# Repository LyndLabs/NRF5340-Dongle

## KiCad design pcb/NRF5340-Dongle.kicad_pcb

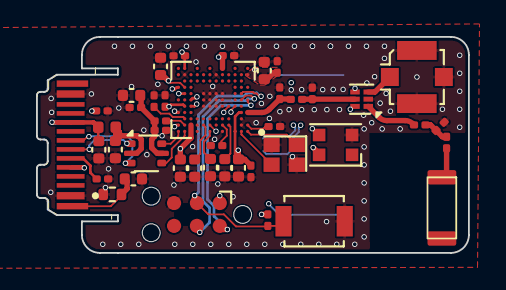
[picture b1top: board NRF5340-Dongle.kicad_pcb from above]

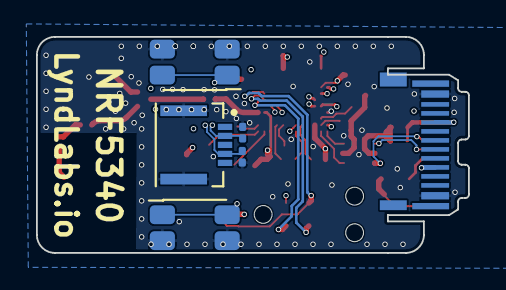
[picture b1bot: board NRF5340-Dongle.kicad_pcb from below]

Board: 4 copper layers, 24.0 x 12.0 mm, 48 parts (5 on the bottom side), 35 nets.

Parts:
AE1: 2450AT18B100
C1, C2, C3, C4, C6, C32, C46: 100nF; C_0201_0603Metric
C8, C9, C20, C30, C43, C45, C47, C47#2: 1uF; C_0402_1005Metric
C10, C16: 4.7uf; C_0201_0603Metric
C11, C21: .7pF; C_0201_0603Metric
C13: 2.2pF; C_0201_0603Metric
C18: NC; R_0201_0603Metric
C24: 4.7nF; C_0402_1005Metric
C25: 10nF; C_0402_1005Metric
C27: 100nF; C_0402_1005Metric
C41, C42: 300pF; C_0201_0603Metric
C44: 2.2nF; C_0201_0603Metric
D2: WS2812B-2020; LED_WS2812B-2020_PLCC4_2.0x2.0mm
J1: Molex 51281-0594; MOLEX_51281-0594
J3: SWD; Tag-Connect_TC2030-IDC-NL_2x03_P1.27mm_Vertical
J6: u.fl; U.FL_Molex_MCRF_73412-0110_Vertical
L1: 4.7nh; L_0201_0603Metric
L4: 2.2nH; L_0201_0603Metric
L5: 120R; L_0402_1005Metric
P1: USB_C_Plug; JAE_DX07P024AJ1R1500
R1: 2.2; R_0201_0603Metric
R2: 1M0; R_0402_1005Metric
R3: 10K; R_0201_0603Metric
R4, R5: 5.1K; R_0201_0603Metric
SW1, SW2: SW_Push; SW_SPST_EVQP7A
SW3: Reset; SW_SPST_B3U-1000P
U1: nRF5340-CLXX; NRF5340-4x4
U2: USBLC6-2P6; SOT-666
U3: DFN-6_1.3x1.2mm_P0.4mm
Y1: 32MHz; Crystal_SMD_2016-4Pin_2.0x1.6mm

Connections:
CC1: P1.A5 (CC), R5.1
DECR: C20.2, U1.B4 (DECR)
DIN+: P1.A6 (D+), U2.1 (I/O1)
DIN-: P1.A7 (D-), U2.3 (I/O2)
GND: C1.1, C2.1, C3.1, C4.1, C6.1, C8.1, C9.1, C10.2, C11.2, C16.2, C18.2, C20.1, C21.2, C24.2, C25.2, C27.2, C30.2, C32.2, C41.1, C42.2, C43.2, C44.2, C45.2, C46.2, C47.1, C47#2.1, D2.2 (VSS), J1.SH (Shield), J3.5 (GND), J6.2 (Ext), P1.A1 (GND), P1.A12 (GND), P1.B1 (GND), P1.B12 (GND), R2.2, R4.2, R5.2, SW1.2, SW2.2, SW3.2, U1.A5 (VSS), U1.B2 (VSS), U1.B9 (VSS), U1.C2 (VSS), U1.D12 (VSS), U1.E5 (VSS), U1.E6 (VSS), U1.E7 (VSS), U1.E8 (VSS), U1.F5 (VSS), U1.F6 (VSS), U1.F7 (VSS), U1.F8 (VSS), U1.G5 (AVSS), U1.G6 (VSS), U1.G7 (VSS), U1.G8 (VSS), U1.K6 (AVSS), U1.K11 (AVSS), U3.2 (GND), Y1.2, Y1.4
LED: D2.3 (DIN), U1.E3 (P0.28/AIN7)
NFC1: C41.2, J1.4, U1.G11 (P0.02/NFC1)
NFC2: C42.1, J1.2, U1.H12 (P0.03/NFC2)
unnamed: AE1.1 (A), L1.1
unnamed: C11.1, C13.1, L1.2
unnamed: C25.1, L5.1, P1.A4 (VBUS), P1.A9 (VBUS), P1.B4 (VBUS), P1.B9 (VBUS)
unnamed: J6.1 (In), U3.3 (RF1)
unnamed: C24.1, P1.S2, R2.1
unnamed: C21.1, L4.2, U1.D1 (ANT)
unnamed: U1.A1 (XC1), Y1.1
unnamed: U1.A2 (XC2), Y1.3
unnamed: C45.1, U1.B8 (DECA)
unnamed: C43.1, U1.A7 (DECD)
unnamed: C46.1, U1.B5 (DECN)
unnamed: C44.1, U1.B1 (DECRF)
unnamed: C16.1, U1.C11 (DECUSB)
unnamed: R1.1, U1.B11 (VBUS)
unnamed: C27.1, L5.2, U2.2 (GND)
unnamed: C18.1, L4.1, U3.5 (ANT)
unnamed: C13.2, U3.1 (RF2)
RST: J3.3 (~RESET), R3.1, SW3.1, U1.G2 (~RESET)
SWCLK: J3.4 (SWCLK), U1.F2 (SWDCLK)
SWDIO: J3.2 (SWDIO), U1.F1 (SWDIO)
USB_D+: U1.A12 (D+), U2.6 (I/O1)
USB_D-: U1.A11 (D-), U2.4 (I/O2)
VBUS: C10.1, C30.1, C32.1, R1.2, U2.5 (VBUS)
VCTL: U1.E4 (P1.10), U3.6 (VCTL)
VDD_NRF: C1.2, C2.2, C3.2, C4.2, C6.2, C8.2, C9.2, C47.2, C47#2.2, D2.4 (VDD), J3.1 (VCC), R3.2, U1.A3 (VDD), U1.B7 (VDD), U1.B10 (VDD), U1.B12 (VDDH), U1.D2 (VDD), U1.E11 (VDD), U1.H11 (VDD), U1.K1 (VDD), U1.L5 (VDD), U1.L11 (VDD), U3.4 (VDD)
VOL-A: SW1.1, U1.E10 (P1.01)
VOL-B: SW2.1, U1.F10 (P0.05/AIN1)

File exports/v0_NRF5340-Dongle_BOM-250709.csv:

Designator,Comment,Footprint,JLCPCB Part #
AE1,2450AT18B100,2450AT18B100,C2917717
"C1,C2,C4,C6,C7,C32,C46",100nF,201,C76934
"C8,C9,C20,C30,C43,C45,C47",1uF,402,C29266
"C10,C16",4.7uf,Capacitor_SMD:C_0201_0603Metric,C335103
C11,.7pF,Capacitor_SMD:C_0201_0603Metric,C907945
C13,2.2pF,Capacitor_SMD:C_0201_0603Metric,C5182465
C21,.7pF,Resistor_SMD:R_0201_0603Metric,C907945
C25,10nF,Capacitor_SMD:C_0402_1005Metric,C15195
C27,100nF,Capacitor_SMD:C_0402_1005Metric,C77020
C44,2.2nF,Capacitor_SMD:C_0201_0603Metric,C161488
D2,WS2812B-2020,LED_SMD:LED_WS2812B-2020_PLCC4_2.0x2.0mm,C965555
J6,u.fl,Connector_Coaxial:U.FL_Molex_MCRF_73412-0110_Vertical,C434808
L1,4.7nh,Inductor_SMD:L_0201_0603Metric,C86126
L4,2.2nH,Inductor_SMD:L_0201_0603Metric,C2043966
L5,120R,Inductor_SMD:L_0402_1005Metric,C76891
P1,DX07P024AJ1R1500,DX07P024AJ1R1500,C5352764
R1,2.2,Resistor_SMD:R_0201_0603Metric,C473517
R3,10K,Resistor_SMD:R_0201_0603Metric,C106225
"R4,R5",5.1K,Resistor_SMD:R_0201_0603Metric, C274341
SW3,Reset,Button_Switch_SMD:SW_SPST_B3U-1000P,C231329
U1,nRF5340-CLXX,LyndLabs:NRF5340-4x4,C3606597
U2,USBLC6-2P6,Package_TO_SOT_SMD:SOT-666,C15999
U3,BGS12P2L6E6327,XFDFN-6,C3312945
Y1,32MHz,Crystal:Crystal_SMD_2016-4Pin_2.0x1.6mm,C2965584

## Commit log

2025-06-09 push v0 files
2025-07-31 dfm improvements
